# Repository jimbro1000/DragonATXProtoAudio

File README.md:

# Dragon 32 ATX Prototype Audio

This repository contains the KiCad project files
to produce the Audio component board for my
ATX Prototype backplane.

This design requires the ATX backplane board in order 
to operate
See https://github.com/jimbro1000/DragonATXProto

## Notes

Revision 1 includes provision for two emulated AY 
sound generators. Each is dedicated to one stereo
channel, both are mixed to create a single central
channel for output over the regular composite
monitor output.

The board can be implemented with just the left
sound generator.

This design has been completed using KiCad 9. Earlier
versions of KiCad are not compatible.

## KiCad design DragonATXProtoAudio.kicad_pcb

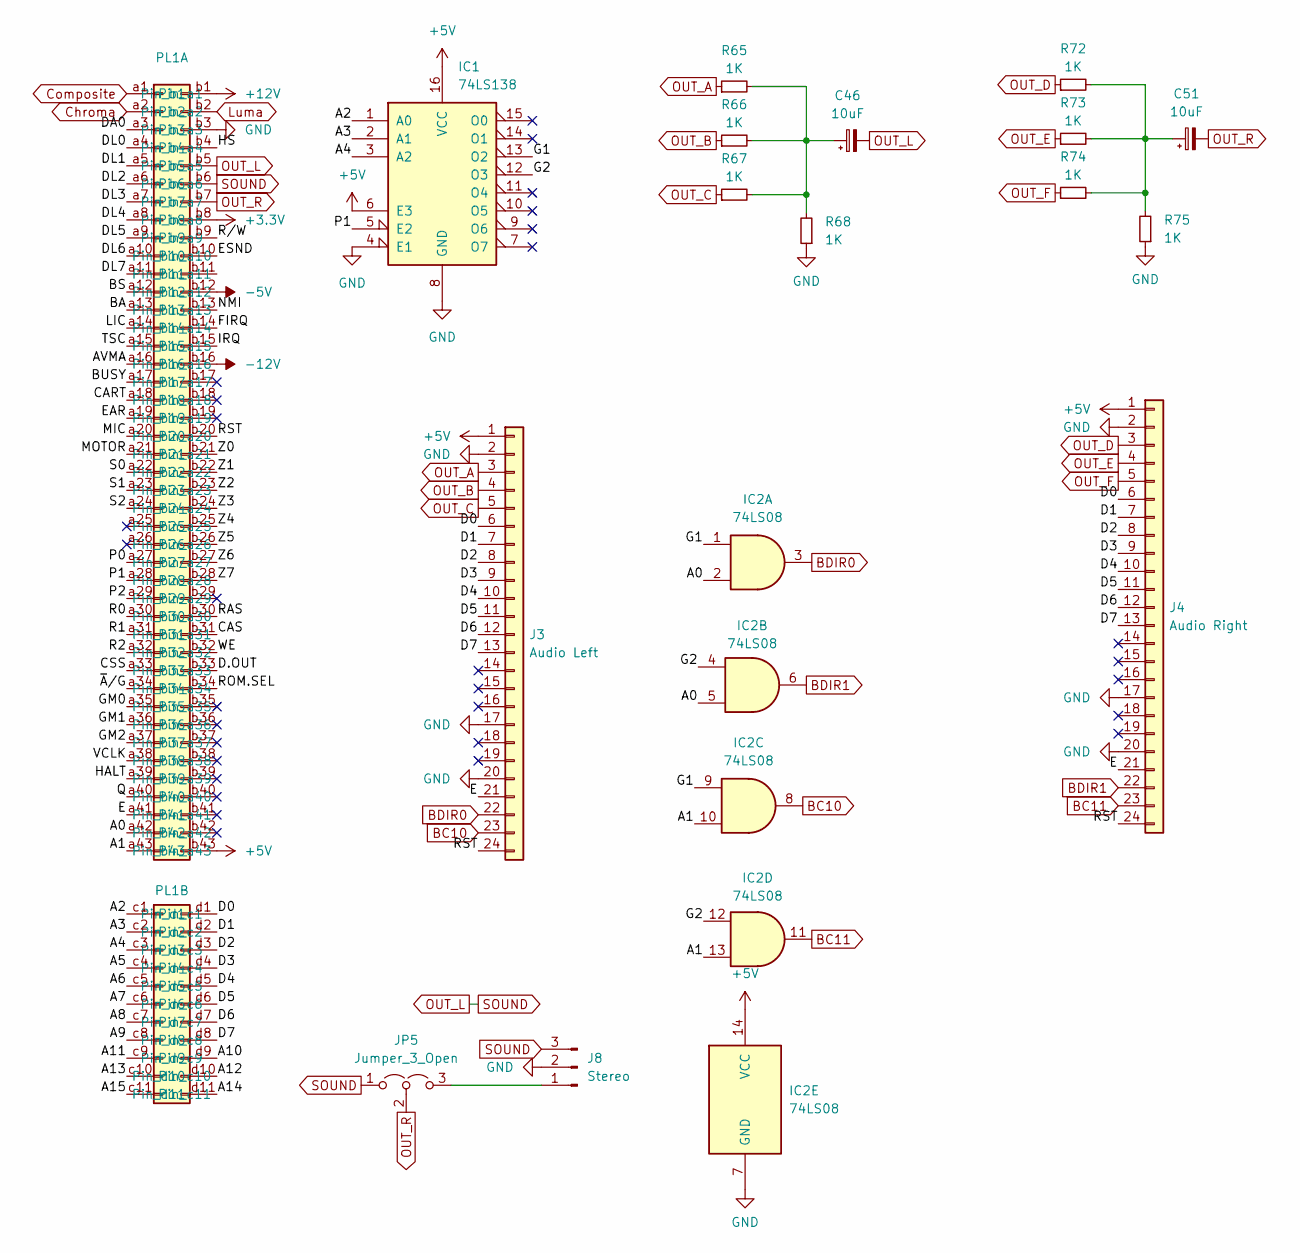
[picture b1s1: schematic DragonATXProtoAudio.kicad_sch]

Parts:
C46, C51: 10uF; CP_Radial_D8.0mm_P5.00mm
IC1: 74LS138; DIP-16_W7.62mm
IC2: 74LS08; DIP-14_W7.62mm
J3: Audio Left; AY-QTHT
J4: Audio Right; AY-QTHT
J8: Stereo; PinHeader_1x03_P2.54mm_Vertical
JP5: Jumper_3_Open; PinHeader_1x03_P2.54mm_Vertical
PL1: Card_Edge
R65, R66, R67, R68, R72, R73, R74, R75: 1K; R_Axial_DIN0204_L3.6mm_D1.6mm_P2.54mm_Vertical

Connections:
+3.3V: PL1.b8
+5V: IC1.6 (E3), IC1.16 (VCC), IC2.14 (VCC), J3.1, J4.1, PL1.b43
+12V: PL1.b1
-5V: PL1.b12
-12V: PL1.b16
/A0: IC2.2, IC2.5, PL1.a42
/A1: IC2.10, IC2.13, PL1.a43
/A2: IC1.1 (A0), PL1.c1
/A3: IC1.2 (A1), PL1.c2
/A4: IC1.3 (A2), PL1.c3
/A5: PL1.c4
/A6: PL1.c5
/A7: PL1.c6
/A8: PL1.c7
/A9: PL1.c8
/A10: PL1.d9
/A11: PL1.c9
/A12: PL1.d10
/A13: PL1.c10
/A14: PL1.d11
/A15: PL1.c11
/AVMA: PL1.a16
/BA: PL1.a13
/BS: PL1.a12
/BUSY: PL1.a17
/CART: PL1.a18
/CAS: PL1.b31
/CSS: PL1.a33
/D0: J3.6, J4.6, PL1.d1
/D1: J3.7, J4.7, PL1.d2
/D2: J3.8, J4.8, PL1.d3
/D3: J3.9, J4.9, PL1.d4
/D4: J3.10, J4.10, PL1.d5
/D5: J3.11, J4.11, PL1.d6
/D6: J3.12, J4.12, PL1.d7
/D7: J3.13, J4.13, PL1.d8
/D.OUT: PL1.b33
/DA0: PL1.a3
/DL0: PL1.a4
/DL1: PL1.a5
/DL2: PL1.a6
/DL3: PL1.a7
/DL4: PL1.a8
/DL5: PL1.a9
/DL6: PL1.a10
/DL7: PL1.a11
/E: J3.21, J4.21, PL1.a41
/EAR: PL1.a19
/ESND: PL1.b10
/FIRQ: PL1.b14
/G1: IC1.13 (O2), IC2.1, IC2.9
/G2: IC1.12 (O3), IC2.4, IC2.12
/GM0: PL1.a35
/GM1: PL1.a36
/GM2: PL1.a37
/HALT: PL1.a39
/HS: PL1.b4
/IRQ: PL1.b15
/LIC: PL1.a14
/MIC: PL1.a20
/MOTOR: PL1.a21
/NMI: PL1.b13
/P0: PL1.a27
/P1: IC1.5 (E2), PL1.a28
/P2: PL1.a29
/Q: PL1.a40
/R0: PL1.a30
/R1: PL1.a31
/R2: PL1.a32
/RAS: PL1.b30
/ROM.SEL: PL1.b34
/RST: J3.24, J4.24, PL1.b20
/R/W: PL1.b9
/S0: PL1.a22
/S1: PL1.a23
/S2: PL1.a24
/TSC: PL1.a15
/VCLK: PL1.a38
/WE: PL1.b32
/Z0: PL1.b21
/Z1: PL1.b22
/Z2: PL1.b23
/Z3: PL1.b24
/Z4: PL1.b25
/Z5: PL1.b26
/Z6: PL1.b27
/Z7: PL1.b28
/~A/G: PL1.a34
BC10: IC2.8, J3.23
BC11: IC2.11, J4.23
BDIR0: IC2.3, J3.22
BDIR1: IC2.6, J4.22
Chroma: PL1.a2
Composite: PL1.a1
GND: IC1.4 (E1), IC1.8 (GND), IC2.7 (GND), J3.2, J3.17, J3.20, J4.2, J4.17, J4.20, J8.2, PL1.b3, R68.1, R75.1
Luma: PL1.b2
unnamed: C46.1, R65.2, R66.2, R67.2, R68.2
unnamed: C51.1, R72.2, R73.2, R74.2, R75.2
unnamed: J8.1, JP5.3 (B)
OUT_A: J3.3, R65.1
OUT_B: J3.4, R66.1
OUT_C: J3.5, R67.1
OUT_D: J4.3, R72.1
OUT_E: J4.4, R73.1
OUT_F: J4.5, R74.1
OUT_L: C46.2, J8.3, JP5.1 (A), PL1.b5, PL1.b6
OUT_R: C51.2, JP5.2 (C), PL1.b7

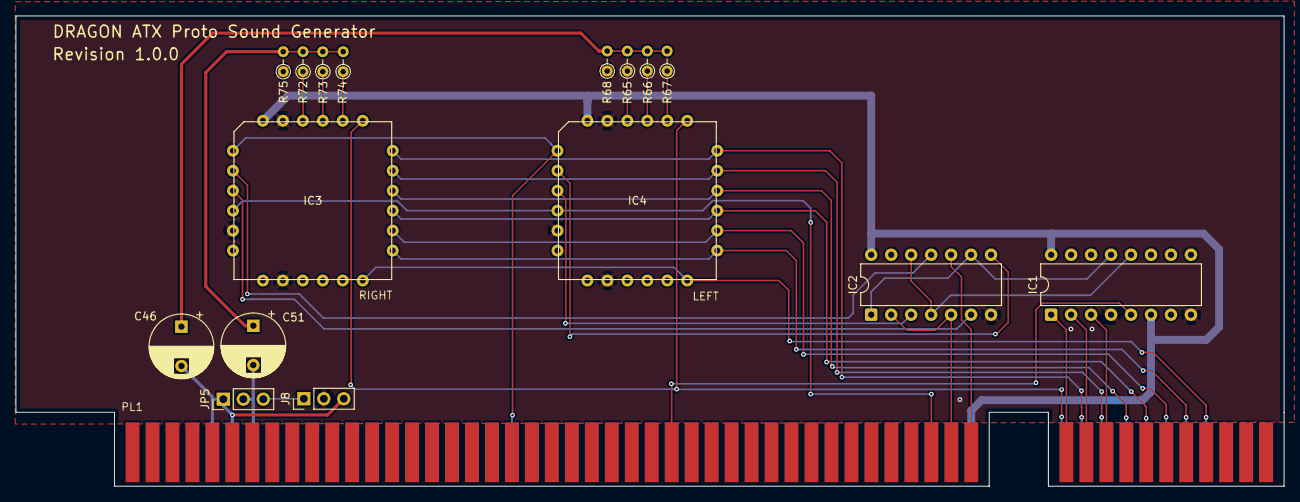
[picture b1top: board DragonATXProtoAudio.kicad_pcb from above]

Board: 2 copper layers, 161.3 x 59.8 mm, 17 parts (0 on the bottom side), 35 nets.

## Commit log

2025-03-17 upgrade card edge spec
2025-03-17 fix routing for new card edge spec
2025-03-17 add iBom
